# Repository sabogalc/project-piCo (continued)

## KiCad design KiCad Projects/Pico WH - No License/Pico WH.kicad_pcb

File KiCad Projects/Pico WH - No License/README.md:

# project piCo W

After a few months of making projects with the Pico, I found myself wanting to utilize some of the features offered by the Pico W. However, this meant that I would need to give the same USB-C reverse-engineering treatment to this board, so I took what I learned from my first go and remade the Pico WH as best I could. 

### Design Sources

- **Schematic:** [Raspberry Pi Pico W Schematic](https://wiki.amperka.ru/_media/products:raspberry-pi-pico-w:raspberry-pi-pico-w-schematic.pdf)
- **PCB Design Files:** [RPi PicoW Files](https://datasheets.raspberrypi.com/picow/RPi-PicoW-PUBLIC-20220607.zip) (Note: This link will download files directly.)

This time, rather than making my own board layout, I tried to follow the factory layout as closely as possible. Similarly to the [Official Files](https://github.com/sabogalc/project-piCo/tree/main/KiCad%20Projects/Pico%20C#official-files) section of the original Type-C Pico, I converted the factory Allegro files into a KiCad file (with an Altium conversion in between the two).

I then used this converted board as the starting point for my board, so the final result is much closer to the original design. Unfortunately, I cannot release either the converted board or my initial design at this time for reasons that I will explain below.

### The Patent

On page 2 of the schematic, there is a note by the antenna arrangement that reads
> The Niche is an Abracon/Proant patented antenna technology. Please contact niche@abracon.com for information on licensing.

I sent an email explaining my project and how it wasn't commercial in any capacity, asking if there was any kind of fee I could pay to be able to release the board as is. The reponse I got read

> The licensed version of Niche is aimed for high volumes (>100kpcs), and there is a royalty fee/pcs which is agreed per project/customer. The idea is that it should be a very cost-effective solution for high-volume production. It is not an open-source solution which can be used without agreement with Abracon.

They did offer an alternative in the form of a stamped metal antenna that worked virtually identically and came with no license requirement, so I remade the board around this footprint (which is the one you can find in this folder). I found the patent [here](https://patentimages.storage.googleapis.com/39/da/99/a6a16469f1c9ba/US10910715.pdf), and though I am not a legal or patent expert, my understanding is that by 35 U.S.C. 154(b), this patent will expire on March 11, 2038, after which I will be okay to release all of the designs.

### Design Process

Though I am not releasing the design that is barred by the patent, I will still show photos of the final version of that board, and I have also released the boardview file for that board (neither one of these are remotely close to a finished PCB, so I'm sure that is fine). Below is a photo of both boards, with the royalty-free design on the left and the closer 1:1 design on the right.

My design process was essentially Alt+Tabbing between a window that had the converted Allegro design and my blank PCB and just building it up piece by piece while following the design specifications from the import. I did have to make some changes in order to get the board manufactured such as slightly decreasing the diameter of the BGA balls for the WiFi chip, but the final result is still very close to the original parameters.

Unfortunately, because of how many vias this board has, the tight routing, and the fact that it is four layers, it costs about $70-75 USD to get 10 of them manufactured, and then to be able to populate them raises the price even more, so it is not very financially sound to order and make this board. Regardless, these design files should still prove useful as an educational resource.

### Component Substitutions

As with the original project piCo, the boot select switch, Schottky diode, and 12MHz crystal in my design are not the exact ones that the Pi Foundation used, but they are compatible substitutes.

### PDF Schematic

A PDF copy of the schematic is available [here](https://github.com/sabogalc/project-piCo/blob/main/KiCad%20Projects/Pico%20WH%20-%20No%20License/Pico%20WH.pdf).

### Board Photos

Below are the renders of the board in KiCad, as well as individual photos of them in real life.

- **KiCad Render - Original:** 
- **KiCad Render - No License:** 

- **Pico WH:** 
- **Pico WH - No License:** 

### Future Enhancements

A version of this board with a non-patented antenna could be developed. Similar designs are available in Chinese clone boards, such as the one in [this AliExpress listing](https://www.aliexpress.com/item/3256805996726845.html). If anyone would like to submit a pull request with changes like this one, I would be happy to merge it.

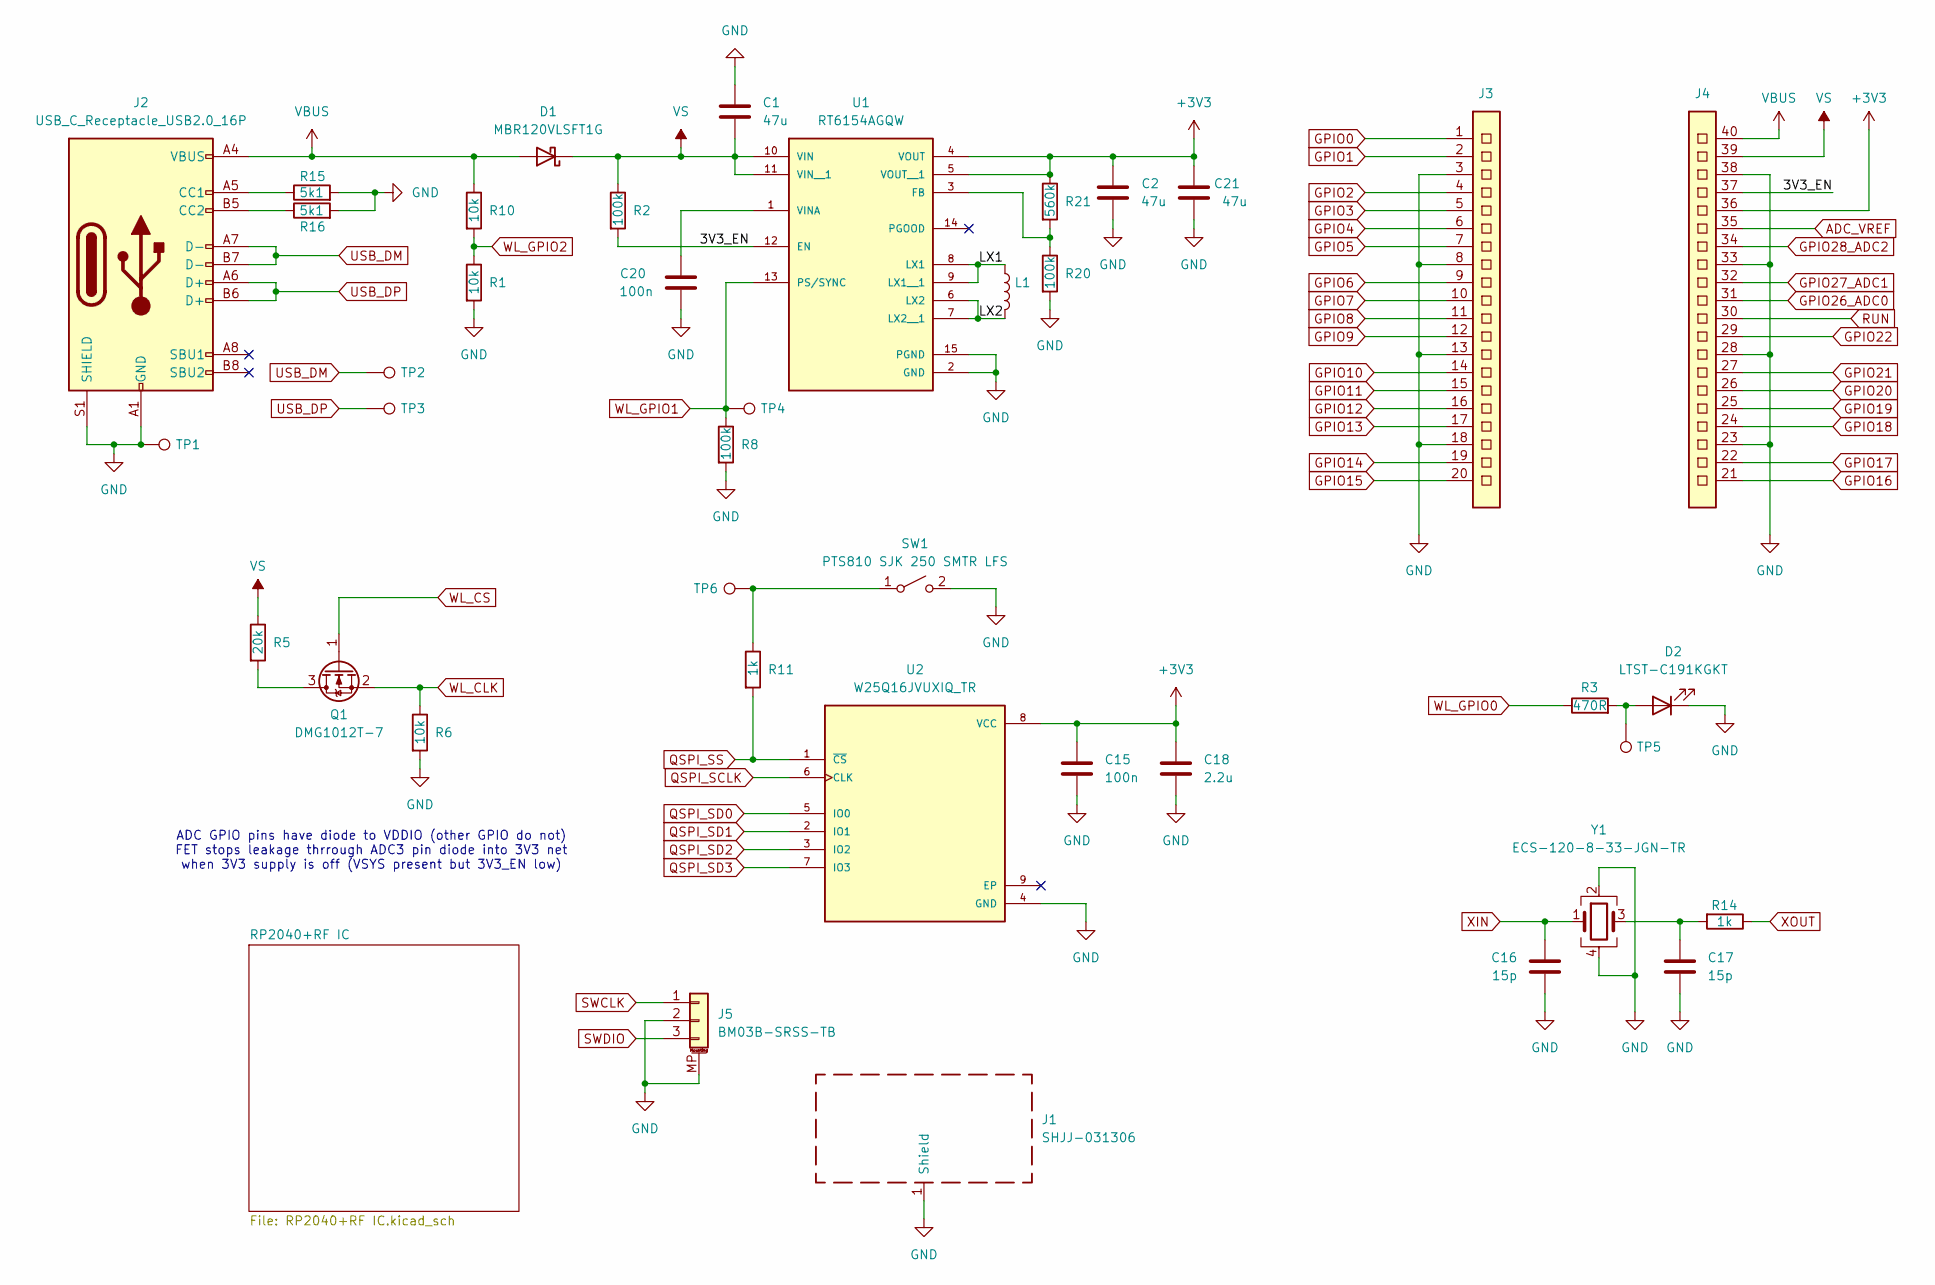
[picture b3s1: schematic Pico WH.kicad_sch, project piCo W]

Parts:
C1, C2, C21: 47u; C_0805_2012Metric
C15, C20: 100n; C_0201_0603Metric
C16, C17: 15p; C_0201_0603Metric
C18: 2.2u; C_0402_1005Metric
D1: MBR120VLSFT1G; D_SOD-123F
D2: LTST-C191KGKT; LED_0603_1608Metric
J1: SHJJ-031306; RF_SHIELD_PICOW
J2: USB_C_Receptacle_USB2.0_16P; USB_C_Receptacle_GCT_USB4105-xx-A_16P_TopMnt_Horizontal
J3: CON_PICO_1-20
J4: CON_PICO_21-40
J5: BM03B-SRSS-TB; JST_SH_BM03B-SRSS-TB_1x03-1MP_P1.00mm_Vertical
L1: SRN2512-1R0M; L_1008_2520Metric
Q1: DMG1012T-7; SOT-523
R1, R6, R10: 10k; R_0201_0603Metric
R2, R8, R20: 100k; R_0201_0603Metric
R3: 470R; R_0201_0603Metric
R5: 20k; R_0201_0603Metric
R11, R14: 1k; R_0201_0603Metric
R15, R16: 5k1; R_0402_1005Metric
R21: 560k; R_0201_0603Metric
SW1: PTS810 SJK 250 SMTR LFS; SW_SPST_PTS810
TP1, TP2, TP3, TP4, TP5, TP6: TestPoint; TestPoint_Pad_1.5x1.5mm
U1: RT6154AGQW; DFN-14-1EP_3x4mm_P0.5mm_EP1.7x3.3mm
U2: W25Q16JVUXIQ_TR; TDFN-8-1EP_3x2mm_P0.5mm_EP1.3x1.4mm
Y1: ECS-120-8-33-JGN-TR; Crystal_SMD_SeikoEpson_FA238-4Pin_3.2x2.5mm

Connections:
+3V3: C2.1, C15.1, C18.1, C21.1, J4.36, R21.1, U1.4 (VOUT), U1.5 (VOUT__1), U2.8 (VCC); also elsewhere on the board
/3V3_EN: J4.37, R2.2, U1.12 (EN)
/LX1: L1.1, U1.8 (LX1), U1.9 (LX1__1)
/LX2: L1.2, U1.6 (LX2), U1.7 (LX2__1)
ADC_VREF: J4.35; also elsewhere on the board
GND: C1.2, C2.2, C15.2, C16.2, C17.2, C18.2, C20.2, C21.2, D2.1 (K), J1.1 (Shield), J2.A1 (GND), J2.A12 (GND), J2.B1 (GND), J2.B12 (GND), J2.S1 (SHIELD), J3.3, J3.8, J3.13, J3.18, J4.23, J4.28, J4.33, J4.38, J5.2, J5.MP (MountPin), R1.2, R6.2, R8.2, R15.2, R16.2, R20.2, SW1.2 (B), TP1.1, U1.2 (GND), U1.15 (PGND), U2.4 (GND), Y1.2, Y1.4; also elsewhere on the board
GPIO0: J3.1; also elsewhere on the board
GPIO1: J3.2; also elsewhere on the board
GPIO2: J3.4; also elsewhere on the board
GPIO3: J3.5; also elsewhere on the board
GPIO4: J3.6; also elsewhere on the board
GPIO5: J3.7; also elsewhere on the board
GPIO6: J3.9; also elsewhere on the board
GPIO7: J3.10; also elsewhere on the board
GPIO8: J3.11; also elsewhere on the board
GPIO9: J3.12; also elsewhere on the board
GPIO10: J3.14; also elsewhere on the board
GPIO11: J3.15; also elsewhere on the board
GPIO12: J3.16; also elsewhere on the board
GPIO13: J3.17; also elsewhere on the board
GPIO14: J3.19; also elsewhere on the board
GPIO15: J3.20; also elsewhere on the board
GPIO16: J4.21; also elsewhere on the board
GPIO17: J4.22; also elsewhere on the board
GPIO18: J4.24; also elsewhere on the board
GPIO19: J4.25; also elsewhere on the board
GPIO20: J4.26; also elsewhere on the board
GPIO21: J4.27; also elsewhere on the board
GPIO22: J4.29; also elsewhere on the board
GPIO26_ADC0: J4.31; also elsewhere on the board
GPIO27_ADC1: J4.32; also elsewhere on the board
GPIO28_ADC2: J4.34; also elsewhere on the board
unnamed: C17.1, R14.2, Y1.3
unnamed: D2.2 (A), R3.2, TP5.1
unnamed: J2.A5 (CC1), R15.1
unnamed: J2.B5 (CC2), R16.1
unnamed: Q1.3 (D), R5.2
unnamed: R11.1, SW1.1 (A), TP6.1
unnamed: R20.1, R21.2, U1.3 (FB)
unnamed: C20.1, U1.1 (VINA)
QSPI_SCLK: U2.6 (CLK); also elsewhere on the board
QSPI_SD0: U2.5 (IO0); also elsewhere on the board
QSPI_SD1: U2.2 (IO1); also elsewhere on the board
QSPI_SD2: U2.3 (IO2); also elsewhere on the board
QSPI_SD3: U2.7 (IO3); also elsewhere on the board
QSPI_SS: R11.2, U2.1 (~CS); also elsewhere on the board
RUN: J4.30; also elsewhere on the board
SWCLK: J5.1; also elsewhere on the board
SWDIO: J5.3; also elsewhere on the board
USB_DM: J2.A7 (D-), J2.B7 (D-), TP2.1; also elsewhere on the board
USB_DP: J2.A6 (D+), J2.B6 (D+), TP3.1; also elsewhere on the board
VBUS: D1.2 (A), J2.A4 (VBUS), J2.A9 (VBUS), J2.B4 (VBUS), J2.B9 (VBUS), J4.40, R10.1
VS: C1.1, D1.1 (K), J4.39, R2.1, R5.1, U1.10 (VIN), U1.11 (VIN__1)
WL_CLK: Q1.2 (S), R6.1; also elsewhere on the board
WL_CS: Q1.1 (G); also elsewhere on the board
WL_GPIO0: R3.1; also elsewhere on the board
WL_GPIO1: R8.1, TP4.1, U1.13 (PS/SYNC); also elsewhere on the board
WL_GPIO2: R1.1, R10.2; also elsewhere on the board
XIN: C16.1, Y1.1; also elsewhere on the board
XOUT: R14.1; also elsewhere on the board

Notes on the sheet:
ADC GPIO pins have diode to VDDIO (other GPIO do not) FET stops leakage thrrough ADC3 pin diode into 3V3 net when 3V3 supply is off (VSYS present but 3V3_EN low)

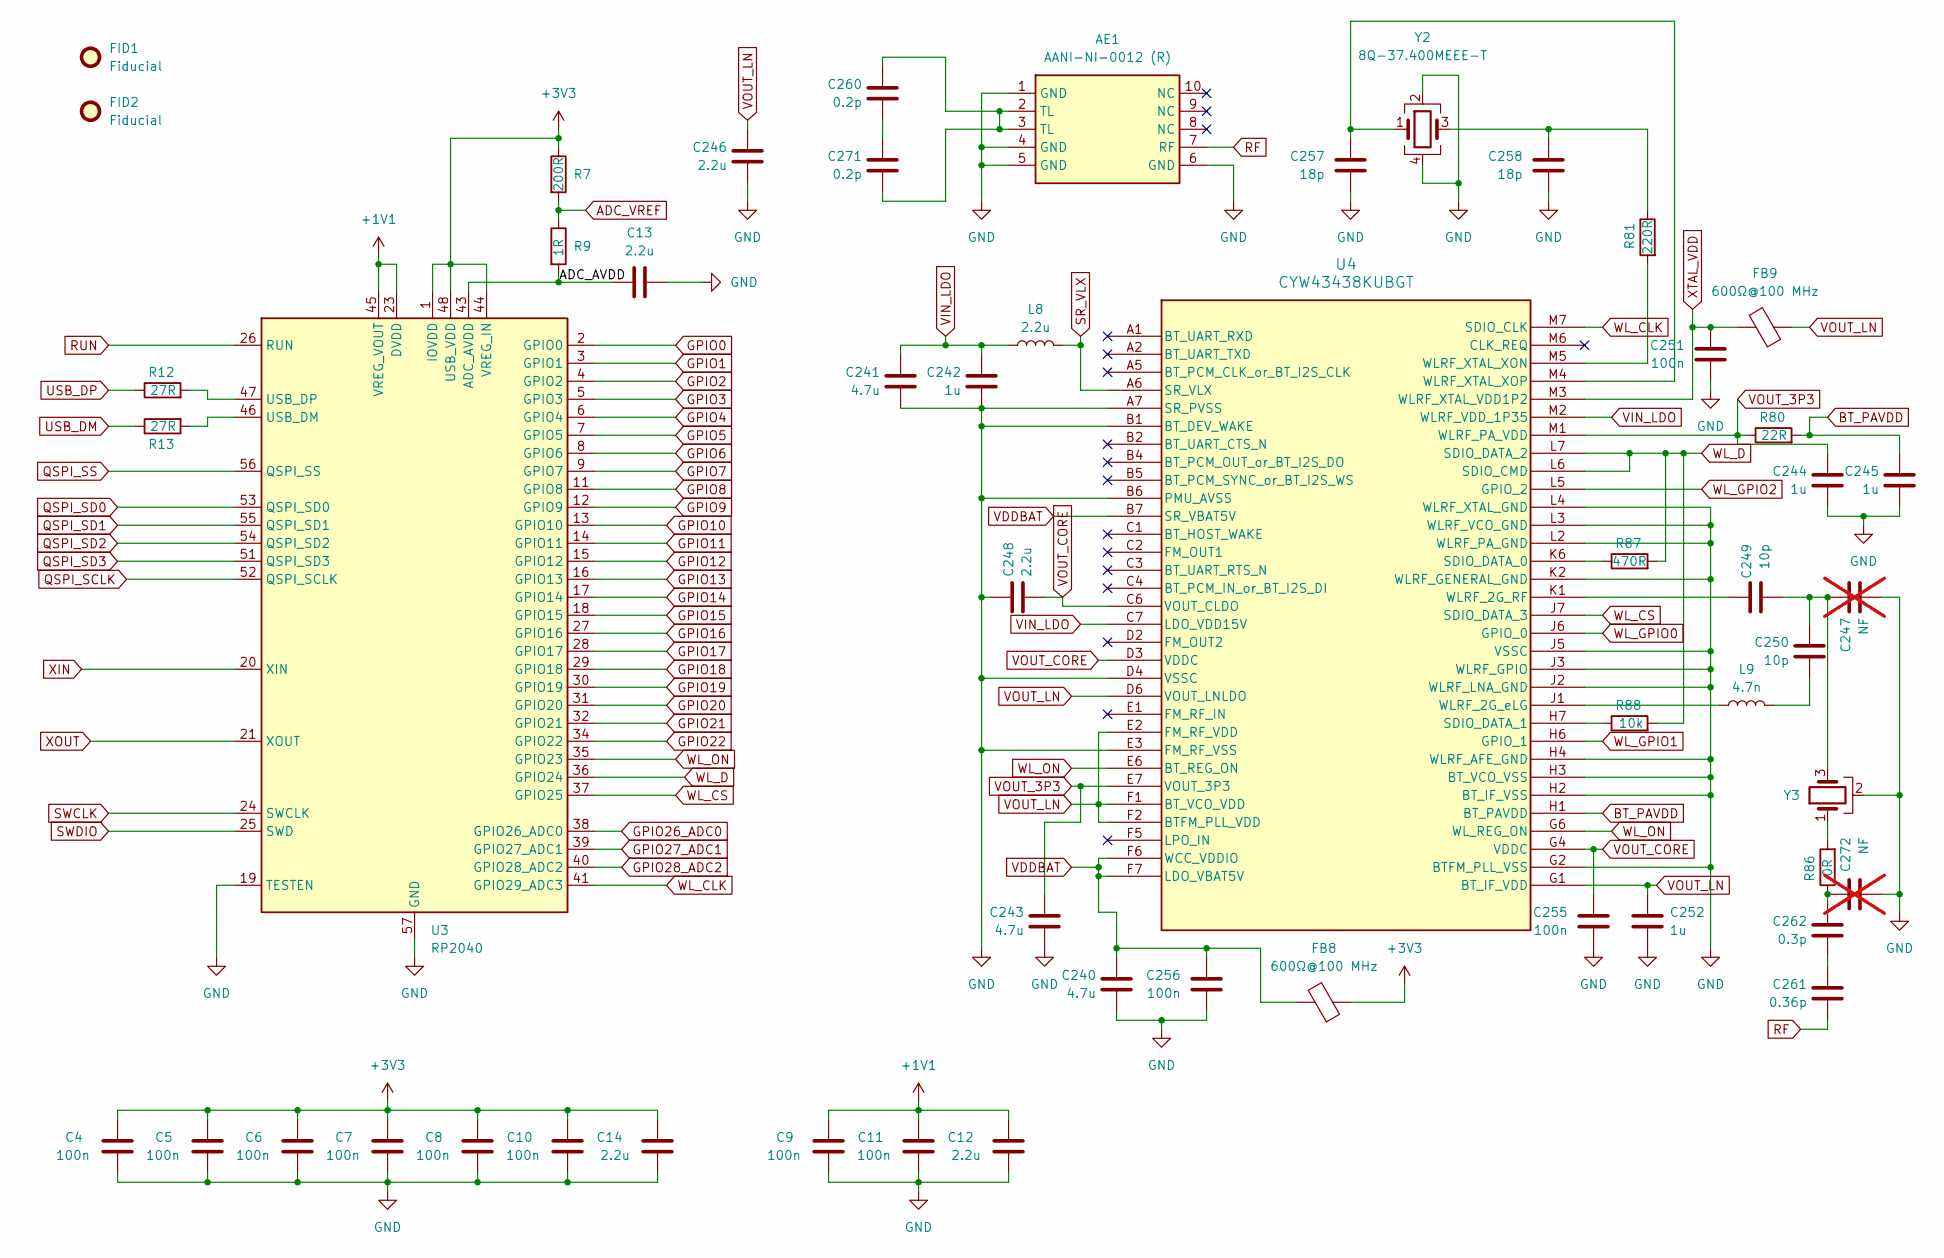
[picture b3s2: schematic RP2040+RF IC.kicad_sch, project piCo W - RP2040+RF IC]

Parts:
AE1: AANI-NI-0012 (R); AANI-NI-0012
C4, C5, C6, C7, C8, C9, C10, C11, C251, C255, C256: 100n; C_0201_0603Metric
C12, C13, C14, C246, C248: 2.2u; C_0402_1005Metric
C240, C241, C243: 4.7u; C_0402_1005Metric
C242, C244, C245, C252: 1u; C_0201_0603Metric
C247, C272: NF; C_0201_0603Metric; not fitted
C249, C250: 10p; C_0201_0603Metric
C257, C258: 18p; C_0201_0603Metric
C260, C271: 0.2p; C_0402_1005Metric
C261: 0.36p; C_0402_1005Metric
C262: 0.3p; C_0402_1005Metric
FB8: 600Ω@100 MHz; L_0603_1608Metric
FB9: 600Ω@100 MHz; L_0201_0603Metric
FID1, FID2: Fiducial; Fiducial_1mm_Mask2mm
L8: 2.2u; L_0603_1608Metric
L9: 4.7n; L_0201_0603Metric
R7: 200R; R_0603_1608Metric
R9: 1R; R_0402_1005Metric
R12, R13: 27R; R_0201_0603Metric
R80: 22R; R_0201_0603Metric
R81: 220R; R_0201_0603Metric
R86: 0R; R_0201_0603Metric
R87: 470R; R_0201_0603Metric
R88: 10k; R_0201_0603Metric
U3: RP2040; QFN-56-1EP_7x7mm_P0.4mm_EP3.2x3.2mm
U4: CYW43438KUBGT; BGA-63
Y2: 8Q-37.400MEEE-T; Oscillator_SMD_Abracon_ASCO-4Pin_1.6x1.2mm
Y3: LFB212G45CG7D227; FILS3_MUR_LFB21XXCG2Q

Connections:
+1V1: C9.1, C11.1, C12.1, U3.23 (DVDD), U3.45 (VREG_VOUT), U3.50 (DVDD)
+3V3: C4.1, C5.1, C6.1, C7.1, C8.1, C10.1, C14.1, FB8.1, R7.1, U3.1 (IOVDD), U3.10 (IOVDD), U3.22 (IOVDD), U3.33 (IOVDD), U3.42 (IOVDD), U3.44 (VREG_IN), U3.48 (USB_VDD), U3.49 (IOVDD); also elsewhere on the board
/RP2040+RF IC/ADC_AVDD: C13.1, R9.2, U3.43 (ADC_AVDD)
ADC_VREF: R7.2, R9.1; also elsewhere on the board
BT_PAVDD: C245.1, R80.2, U4.H1 (BT_PAVDD)
GND: AE1.1 (GND), AE1.4 (GND), AE1.5 (GND), AE1.6 (GND), C4.2, C5.2, C6.2, C7.2, C8.2, C9.2, C10.2, C11.2, C12.2, C13.2, C14.2, C240.2, C241.2, C242.2, C243.2, C244.2, C245.2, C246.2, C247.1, C248.2, C251.2, C252.2, C255.2, C256.2, C257.2, C258.2, C272.2, U3.19 (TESTEN), U3.57 (GND), U4.A7 (SR_PVSS), U4.B1 (BT_DEV_WAKE), U4.B6 (PMU_AVSS), U4.D4 (VSSC), U4.E3 (FM_RF_VSS), U4.G2 (BTFM_PLL_VSS), U4.H2 (BT_IF_VSS), U4.H3 (BT_VCO_VSS), U4.H4 (WLRF_AFE_GND), U4.J2 (WLRF_LNA_GND), U4.J3 (WLRF_GPIO), U4.J5 (VSSC), U4.K2 (WLRF_GENERAL_GND), U4.L2 (WLRF_PA_GND), U4.L3 (WLRF_VCO_GND), U4.L4 (WLRF_XTAL_GND), Y2.2, Y2.4, Y3.2; also elsewhere on the board
GPIO0: U3.2 (GPIO0); also elsewhere on the board
GPIO1: U3.3 (GPIO1); also elsewhere on the board
GPIO2: U3.4 (GPIO2); also elsewhere on the board
GPIO3: U3.5 (GPIO3); also elsewhere on the board
GPIO4: U3.6 (GPIO4); also elsewhere on the board
GPIO5: U3.7 (GPIO5); also elsewhere on the board
GPIO6: U3.8 (GPIO6); also elsewhere on the board
GPIO7: U3.9 (GPIO7); also elsewhere on the board
GPIO8: U3.11 (GPIO8); also elsewhere on the board
GPIO9: U3.12 (GPIO9); also elsewhere on the board
GPIO10: U3.13 (GPIO10); also elsewhere on the board
GPIO11: U3.14 (GPIO11); also elsewhere on the board
GPIO12: U3.15 (GPIO12); also elsewhere on the board
GPIO13: U3.16 (GPIO13); also elsewhere on the board
GPIO14: U3.17 (GPIO14); also elsewhere on the board
GPIO15: U3.18 (GPIO15); also elsewhere on the board
GPIO16: U3.27 (GPIO16); also elsewhere on the board
GPIO17: U3.28 (GPIO17); also elsewhere on the board
GPIO18: U3.29 (GPIO18); also elsewhere on the board
GPIO19: U3.30 (GPIO19); also elsewhere on the board
GPIO20: U3.31 (GPIO20); also elsewhere on the board
GPIO21: U3.32 (GPIO21); also elsewhere on the board
GPIO22: U3.34 (GPIO22); also elsewhere on the board
GPIO26_ADC0: U3.38 (GPIO26_ADC0); also elsewhere on the board
GPIO27_ADC1: U3.39 (GPIO27_ADC1); also elsewhere on the board
GPIO28_ADC2: U3.40 (GPIO28_ADC2); also elsewhere on the board
unnamed: AE1.2 (TL), AE1.3 (TL), C260.1, C271.2
unnamed: C247.2, C249.1, C250.1, Y3.3
unnamed: C250.2, L9.1
unnamed: C258.1, R81.1, Y2.3
unnamed: C260.2, C271.1
unnamed: C261.1, C262.1
unnamed: C262.2, C272.1, R86.1
unnamed: R86.2, Y3.1
unnamed: R13.2, U3.46 (USB_DM)
unnamed: R12.2, U3.47 (USB_DP)
unnamed: R87.1, U4.K6 (SDIO_DATA_0)
unnamed: R88.1, U4.H7 (SDIO_DATA_1)
unnamed: C249.2, U4.K1 (WLRF_2G_RF)
unnamed: L9.2, U4.J1 (WLRF_2G_eLG)
unnamed: R81.2, U4.M5 (WLRF_XTAL_XON)
unnamed: C257.1, U4.M4 (WLRF_XTAL_XOP), Y2.1
QSPI_SCLK: U3.52 (QSPI_SCLK); also elsewhere on the board
QSPI_SD0: U3.53 (QSPI_SD0); also elsewhere on the board
QSPI_SD1: U3.55 (QSPI_SD1); also elsewhere on the board
QSPI_SD2: U3.54 (QSPI_SD2); also elsewhere on the board
QSPI_SD3: U3.51 (QSPI_SD3); also elsewhere on the board
QSPI_SS: U3.56 (QSPI_SS); also elsewhere on the board
RF: AE1.7 (RF), C261.2
RUN: U3.26 (RUN); also elsewhere on the board
SR_VLX: L8.1, U4.A6 (SR_VLX)
SWCLK: U3.24 (SWCLK); also elsewhere on the board
SWDIO: U3.25 (SWD); also elsewhere on the board
USB_DM: R13.1; also elsewhere on the board
USB_DP: R12.1; also elsewhere on the board
VDDBAT: C240.1, C256.1, FB8.2, U4.B7 (SR_VBAT5V), U4.F6 (WCC_VDDIO), U4.F7 (LDO_VBAT5V)
VIN_LDO: C241.1, C242.1, L8.2, U4.C7 (LDO_VDD15V), U4.M2 (WLRF_VDD_1P35)
VOUT_3P3: C243.1, C244.1, R80.1, U4.E7 (VOUT_3P3), U4.M1 (WLRF_PA_VDD)
VOUT_CORE: C248.1, C255.1, U4.C6 (VOUT_CLDO), U4.D3 (VDDC), U4.G4 (VDDC)
VOUT_LN: C246.1, C252.1, FB9.1, U4.D6 (VOUT_LNLDO), U4.E2 (FM_RF_VDD), U4.F1 (BT_VCO_VDD), U4.F2 (BTFM_PLL_VDD), U4.G1 (BT_IF_VDD)
WL_CLK: U3.41 (GPIO29_ADC3), U4.M7 (SDIO_CLK); also elsewhere on the board
WL_CS: U3.37 (GPIO25), U4.J7 (SDIO_DATA_3); also elsewhere on the board
WL_D: R87.2, R88.2, U3.36 (GPIO24), U4.L6 (SDIO_CMD), U4.L7 (SDIO_DATA_2)
WL_GPIO0: U4.J6 (GPIO_0); also elsewhere on the board
WL_GPIO1: U4.H6 (GPIO_1); also elsewhere on the board
WL_GPIO2: U4.L5 (GPIO_2); also elsewhere on the board
WL_ON: U3.35 (GPIO23), U4.E6 (BT_REG_ON), U4.G6 (WL_REG_ON)
XIN: U3.20 (XIN); also elsewhere on the board
XOUT: U3.21 (XOUT); also elsewhere on the board
XTAL_VDD: C251.1, FB9.2, U4.M3 (WLRF_XTAL_VDD1P2)

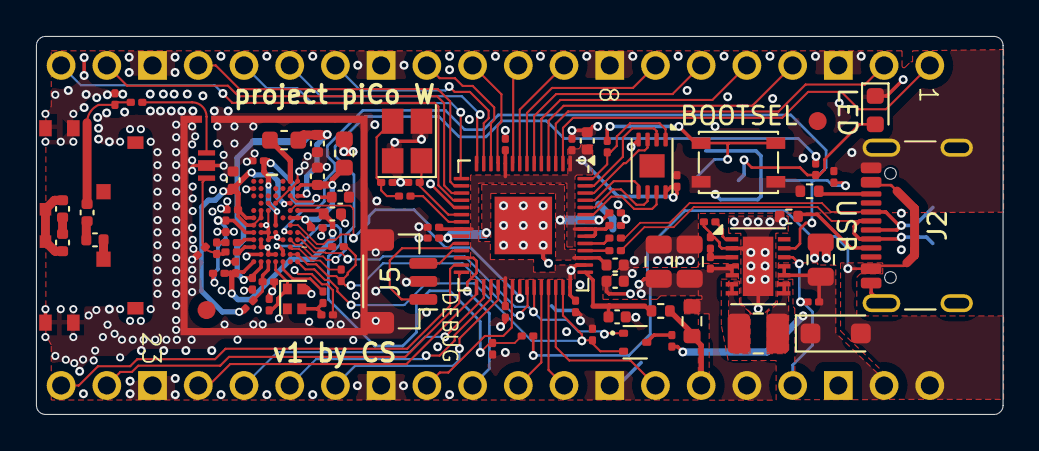
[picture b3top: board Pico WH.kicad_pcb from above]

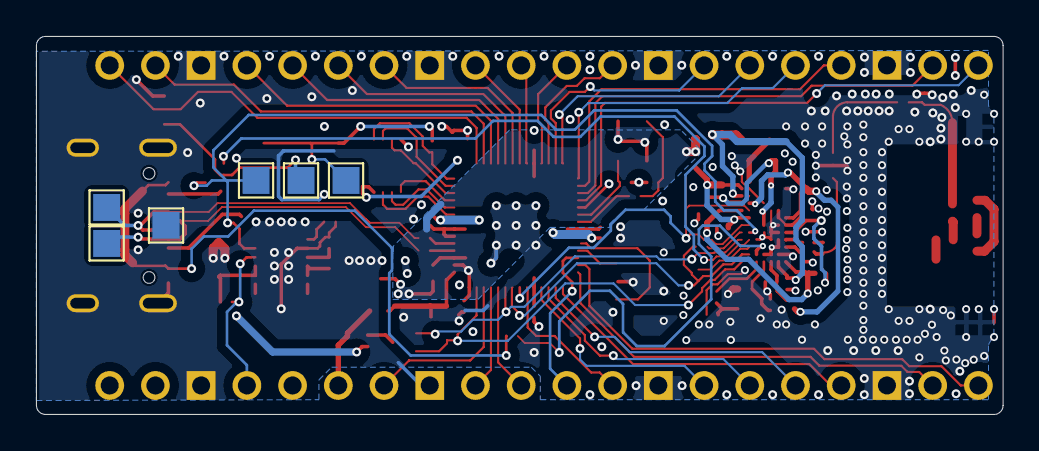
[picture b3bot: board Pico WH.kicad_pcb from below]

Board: 4 copper layers, 53.7 x 21.0 mm, 93 parts (6 on the bottom side), 89 nets.

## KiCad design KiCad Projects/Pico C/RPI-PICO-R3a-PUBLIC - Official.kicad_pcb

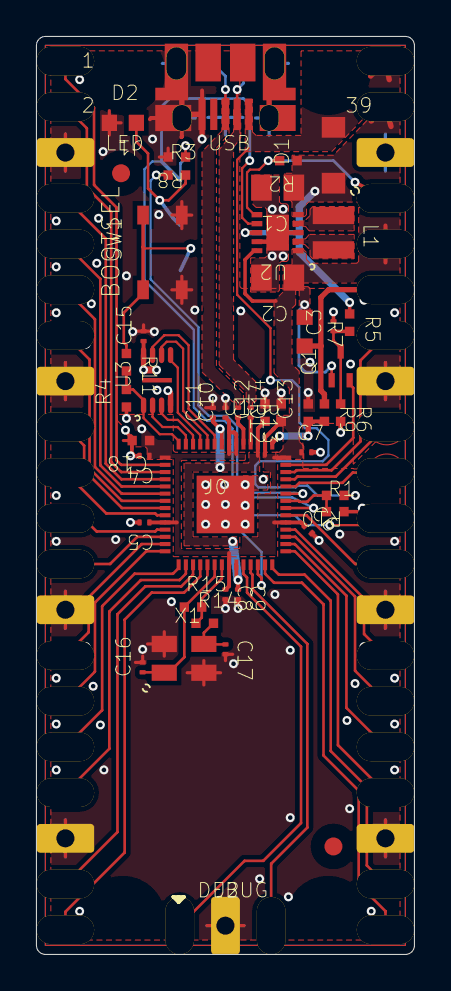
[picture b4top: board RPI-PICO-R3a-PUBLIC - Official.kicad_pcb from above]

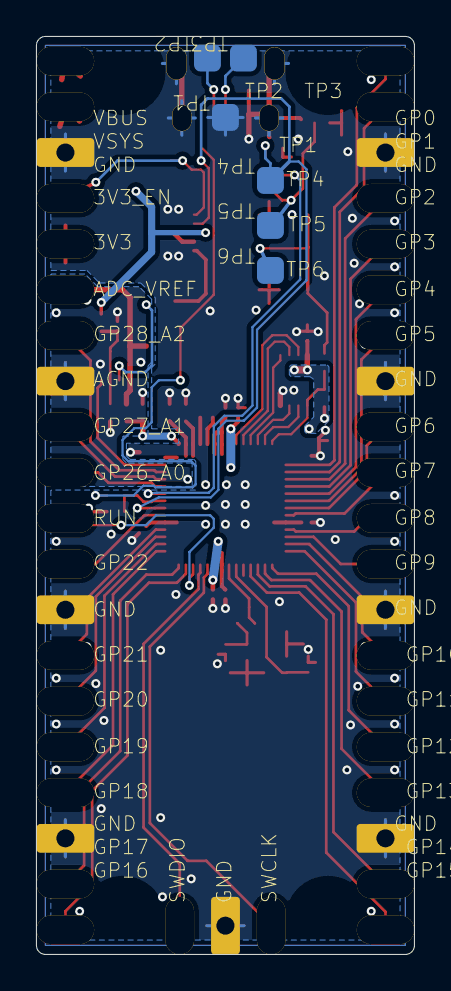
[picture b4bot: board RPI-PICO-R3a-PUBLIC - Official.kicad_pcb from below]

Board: 2 copper layers, 21.0 x 51.0 mm, 51 parts (6 on the bottom side), 59 nets.

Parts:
C1, C2: CAP_MLCC_CAPC2012_47U_RP-019A1P; CAPC2012
C3: CAP_MLCC_M0603_PICO_1N_RP-019A1; M0603_PICO
C4, C5, C6, C7, C8, C9, C10, C11, C15: CAP_MLCC_M0603_PICO_100N_RP-019; M0603_PICO
C12, C13, C14, C18: CAP_MLCC_CAPC1005_2U2_RP-019A1P; CAPC1005
C16, C17: CAP_MLCC_M0603_PICO_15P_RP-019A; M0603_PICO
D1: DIODE_SCHOTTKY_SOD123FL_MBR120V; SOD123FL
D2: LED_2PIN_AVAGO_QSM_GREEN_RP-019; AVAGO_QSM
J0: CON_PICO_40W_CON_PICO_40W_CON_P; CON_PICO_40W
J1: CON_UUSB_B_FCI_10103594-0001LF_; FCI_10103594-0001LF
J2: CON_PICO_3W_CON_PICO_3W_CON_PIC; CON_PICO_3W
L1: INDUCTOR_BOURNS_SRN2512_2U2_RP-; BOURNS_SRN2512
Q1: MOSFET_N_SOT50P160X90-3N_DMG101; SOT50P160X90-3N
R1: RES_CHIP_RESC1005_10K_RP-019A1P; RESC1005
R2, R6, R8: RES_CHIP_RESC1005_100K_RP-019A1; RESC1005
R3: RES_CHIP_RESC1005_470R_RP-019A1; RESC1005
R4, R15: RES_CHIP_RESC1005_NO-FIT_; RESC1005
R5: RES_CHIP_RESC1005_200K_RP-019A1; RESC1005
R7: RES_CHIP_RESC1608_200R_RP-01A5Y; RESC1608
R9: RES_CHIP_RESC1005_1R_RP-019A1P-; RESC1005
R10: RES_CHIP_RESC1005_5K6_RP-019A1P; RESC1005
R11, R14: RES_CHIP_RESC1005_1K_RP-019A1P-; RESC1005
R12, R13: RES_CHIP_M0603_PICO_27R_RP-019A; M0603_PICO
SW1: SW_PB_4PIN_TONEPARTS_TP-1221U-K; TONEPARTS_TP-1221U-K9K5325
TP1, TP2, TP3, TP4, TP5, TP6: TP_SMT_SQUARERC_1P5MM_TP_SMT_1P; TP_SMT_1P5X1P5MM
U1: RPI_RP2040_RPI_RP2040_RP2040; RPI_RP2040
U2: RICHTEK_RT6150_RICHTEK_RT6150B_; RICHTEK_RT6150B
U3: WINBOND_W25X_QSPI_FLASH_USON_US; USON_2X3MM
X1: CRYSTAL_4P_XTAL320X250X100_12MH; XTAL320X250X100

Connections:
1V1: C9.1, C11.1, C12.1, U1.23, U1.45, U1.50
3V3: C2.1, C4.1, C5.1, C6.1, C7.1, C8.1, C10.1, C14.1, C15.1, C18.1, J0.36, Q1.1, R4.1, R7.1, U1.1, U1.10, U1.22, U1.33, U1.42, U1.44, U1.48, U1.49, U2.1, U2.10, U3.8
3V3_EN: J0.37, R2.2, U2.6
ADC_AVDD: C13.1, R9.2, U1.43
ADC_VREF: J0.35, R7.2, R9.1
GND: C1.2, C2.2, C3.2, C4.2, C5.2, C6.2, C7.2, C8.2, C9.2, C10.2, C11.2, C12.2, C13.2, C14.2, C15.2, C16.2, C17.2, C18.2, D2.1, J0.3, J0.8, J0.13, J0.18, J0.23, J0.28, J0.33, J0.38, J1.5, J1.6, J1.7, J1.8, J1.9, J2.2, R1.2, R6.2, R8.2, SW1.3, SW1.4, TP1.1, U1.19, U1.57, U2.3, U2.9, U2.11, U3.4, X1.2, X1.4
GPIO0: J0.1, U1.2
GPIO1: J0.2, U1.3
GPIO2: J0.4, U1.4
GPIO3: J0.5, U1.5
GPIO4: J0.6, U1.6
GPIO5: J0.7, U1.7
GPIO6: J0.9, U1.8
GPIO7: J0.10, U1.9
GPIO8: J0.11, U1.11
GPIO9: J0.12, U1.12
GPIO10: J0.14, U1.13
GPIO11: J0.15, U1.14
GPIO12: J0.16, U1.15
GPIO13: J0.17, U1.16
GPIO14: J0.19, U1.17
GPIO15: J0.20, U1.18
GPIO16: J0.21, U1.27
GPIO17: J0.22, U1.28
GPIO18: J0.24, U1.29
GPIO19: J0.25, U1.30
GPIO20: J0.26, U1.31
GPIO21: J0.27, U1.32
GPIO22: J0.29, U1.34
GPIO23: R8.1, TP4.1, U1.35, U2.7
GPIO24: R1.1, R10.2, U1.36
GPIO25: R3.1, U1.37
GPIO26_ADC0: J0.31, U1.38
GPIO27_ADC1: J0.32, U1.39
GPIO28_ADC2: J0.34, U1.40
GPIO29_ADC3: Q1.2, U1.41
N1248345: L1.1, U2.4
N1248352: L1.2, U2.2
N1283798: D2.2, R3.2, TP5.1
N1286133: C3.1, Q1.3, R5.2, R6.1
N1327876: R11.1, SW1.1, SW1.2, TP6.1
QSPI_SCLK: U1.52, U3.6
QSPI_SD0: U1.53, U3.5
QSPI_SD1: U1.55, U3.2
QSPI_SD2: U1.54, U3.3
QSPI_SD3: U1.51, U3.7
QSPI_SS: R4.2, R11.2, U1.56, U3.1
RUN: J0.30, U1.26
SWCLK: J2.1, U1.24
SWDIO: J2.3, U1.25
USB_DM: J1.2, R13.1, TP2.1
USB_DMX: R13.2, U1.46
USB_DP: J1.3, R12.1, TP3.1
USB_DPX: R12.2, U1.47
VBUS: D1.2, J0.40, J1.1, R10.1
VSYS: C1.1, D1.1, J0.39, R2.1, R5.1, U2.5, U2.8
XIN: C16.1, R15.1, U1.20, X1.1
XOUT: R14.1, R15.2, U1.21
XR: C17.1, R14.2, X1.3

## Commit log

2024-01-25 Add files via upload
    Uploaded project files and license.
2024-01-25 Update README.md
    I've never made a ReadMe before, someone let me know if this one too long.
2024-01-25 Delete Pico C directory
    I edited the silkscreen so I'm purging this and adding the updated one because I don't know how to Git.
2024-01-25 Add files via upload
    Re-added project files.
2024-01-25 Update README.md
    Typos and readability in the ReadMe.
2024-01-25 Update README.md
    Removed the redundant description since I saw it was on the side of the page and specified which version of KiCad I used.
2024-01-25 Update README.md
    For some reason I didn't think to include the word "made" before.
2024-01-27 Delete Pico C directory
    I don't know how to just update the files that are here so I'm going to purge the old directory and upload the new one.
2024-01-27 Add files via upload
    Uploaded version 2 of the board
2024-01-27 Update README.md
    Updated the ReadMe to reflect version 2 of the board.
2024-02-08 Add files via upload
    Uploaded version 3 of the project
2024-02-08 Add files via upload
    Made a slight modification to a GND trace on the W25Q16JVUXIQ.
2024-02-08 Add files via upload
    Importing the project onto another computer caused weird errors with some of the STEP files, so I attempted to correct them and reupload the project.
2024-02-15 Add files via upload
    Corrected the footprint of the 12MHz oscillator.
2024-02-15 Add files via upload
    Corrected USB data lines, confirmed the board functions.
2024-02-27 Add files via upload
    Upload boardview file for use with OpenBoardView.
2024-02-27 Add files via upload
    Changed VSS to VS to reflect that it is a system voltage and not a negative supply/GND.
2024-02-28 Add files via upload
    Updated design and included official design file from the Pi Foundation.
2024-02-28 Update README.md
    Included `RPI-PICO-R3a-PUBLIC - Official.kicad_pcb` description and images.
2024-02-29 Add files via upload
    Slightly adjusted routing on GPIO3.
2024-03-02 Add files via upload
    Corrected pin 33 to actually be GND instead of a NC to GNDA.
2024-03-02 Add files via upload
    Updated gerbers.
2024-03-03 Add files via upload
    Updated component references to more closely match the original Pico.
2024-03-05 Update README.md
    Cropped AliExpress photo.
2024-03-05 Add files via upload
    Changed resistor reference numbers to match the real Pico H.
2024-03-05 Update README.md
    Updated ADC shunt resistor reference name.
2024-03-05 Update README.md
    Updated links to previous commits to be directly within GitHub.
2024-03-05 Update README.md
    Fixed typo.
2024-03-09 Delete Pico C/~RPI-PICO-R3a-PUBLIC.kicad_pcb.lck
    Importing this project would cause an error that the project was open on my computer
2024-03-09 Add files via upload
    Updated X1's footprint for schematic parity in DRC.
2024-03-09 Add files via upload
    Updated RPI-PICO-R3a-PUBLIC - Official.kicad_pcb to KiCad 8.
2024-03-09 Update README.md
    Updated to reflect the project now being based on KiCad 8.
2024-03-12 Add files via upload
    Added Boardview file and OpenBoardData file.
2024-03-23 Upload Boardview+OpenBoardData file for real Pico
2024-04-01 Updated boardview file outlines
    Used a simplified board outline for the boardview files.
2024-05-09 Footprint Modifications
    Changed the footprints to use included KiCad models where possible, removed unnecessary STEP files.
2024-05-09 Update RPI-PICO-R3a-PUBLIC.pdf
    Updated PDF copy of schematic.
2024-05-10 Updated schematic for crystal
    Updated the schematic symbol for the 12MHz crystal to be a KiCad included symbol.
2024-08-01 Added the Pico WH
    Refactored the repository to include the design files for the Pico WH.
2024-08-01 Fixed dead links, added HTML BOM
    I fixed dead links that I made beforehand by prediction and I added an HTML BOM for the USB-C Pico H.
2024-08-14 Added Pico 2
    Added an initial design for the Pico 2. Also updated the original Pico C to v4 (without README update since I'm waiting on boards to ship).
2024-08-27 Updated main Pico to v4
    Updated the documentation to reflect v4 of the original Pico. Also added a `README` for the boardview files.
